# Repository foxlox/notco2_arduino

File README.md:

NotCO2 - A Co2 analyzer for rebreathers
=======================================
fortunato lodari - fox@thebrain.net

If you wish to write me by email, please use the tag [NOTCO2] (with brackets)
in your subject

Please read all DOCs carefully

Project borns in 2011 by a personal need, I'm a mathematical, then I can't leave an independent variable to change my life for a sport.
This independent variable is Carbon Dioxide, CO2. Then I decided to begin a new project to analyze my breathe underwater.

Till today, me and other many peoples are using it with satisfaction by over 6 years.
The sensor is working good for an average life of 5 years.

I received a lot of offers for my project, but I wish to share this with other peoples who want to hack.

Please do not be surprised reading the source code, I'm really (but really!) much more professional and tidy
than you consider me to look at it, it's really simple. It was born to hack, and then when it worked 100% I left it as it is.

It bores me to refine it and I'll not do it just now
that I want to share it ;-)
Now it's your time to refine it, but remember: it really works very well!!!

Documents:

a. layout of PCB and project to build it

b. required hardware components

c. source code HUD (never optimized, discreetly legible, absolutely improvable...)

d. source code Wrist Console (also fot it never optimized, discreetly legible, absolutely improvable...)

e. all DGWs to build your own enclosures with a 3d lathe machine

f. some pics

About CO2 Sensor: I cannot include device's interface specification without owner authorization, but you could try to ask
them: Dynament Ltd - www.dynament.com

  The sensor doesn't suffer with moisture, it's important to stay face down in the loop, and to be dry after diving.

Please, read ALL documents in each folder.

The Author is not responsible for damage to peoples that use this project.
It works perfectly but you must build it perfectly too.

Special thanks to:

Gabriele Paparo for hints, support and test

Martin Tolksdorf for enclosure and wrist project

Domenico Tripodi for support and experience during  diving tests

Saverio Rotella for HUD testing

Massimilaino Salvatori for hints

Sebastiano Pappalardo and Paolo Li Pera of Grade Equipments for HUD, wrist console and sensors enclosures

Gian Ameri for hints and support

Aldo Ferrucci for support

Franco Amadeo for diving support

My wonderful wife Mara for everything!

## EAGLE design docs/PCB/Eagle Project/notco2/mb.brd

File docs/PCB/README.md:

PCB information:
this is the project to build a PCB for NotCo2

Open with Eagles PCB. This release hasn't space for buzzer, could you insert it by yourself on arduino pin 3

connections:

SV2 pin 3, v+ in to battery v+

SV2 pin 1, v- -> to reed bulb -> to battery v-

SV2 pin 5, sensor tx

SV2 pin 6, sensor rx

Display

SV1 pin 1 TFT display VIN

SV1 pin 2 TFT display Ground

SV1 pin 3 RST

SV1 pin 4 RS

SV1 pin 5 SDA

SV1 pin 6 SDL

SV1 pin 7 CS

SV1 pin 8 TFT display VD33

HUD

SV2 pin 4, DIN

SV2 pin 3, led module v+

SV5 pin 2, led module v-

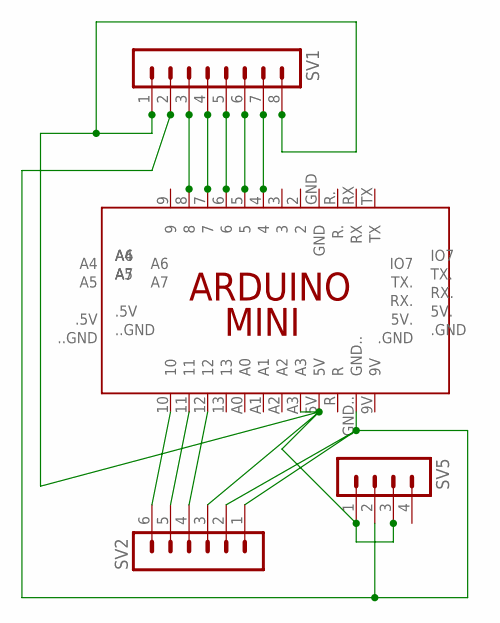
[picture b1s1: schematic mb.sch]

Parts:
PCB2: ARDUINO_MINI
SV1: MA08-1W
SV2: MA06-1
SV5: MA04-1

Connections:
unnamed: PCB2.8, SV1.3
unnamed: PCB2.7, SV1.4
unnamed: PCB2.6, SV1.5
unnamed: PCB2.5, SV1.6
unnamed: PCB2.4, SV1.7
unnamed: PCB2.5V, PCB2.A3, SV1.1, SV1.8, SV2.3, SV5.1, SV5.3
unnamed: PCB2.12, SV2.4
unnamed: PCB2.GND.., SV1.2, SV2.1, SV2.2, SV5.2
unnamed: PCB2.11, SV2.5
unnamed: PCB2.10, SV2.6

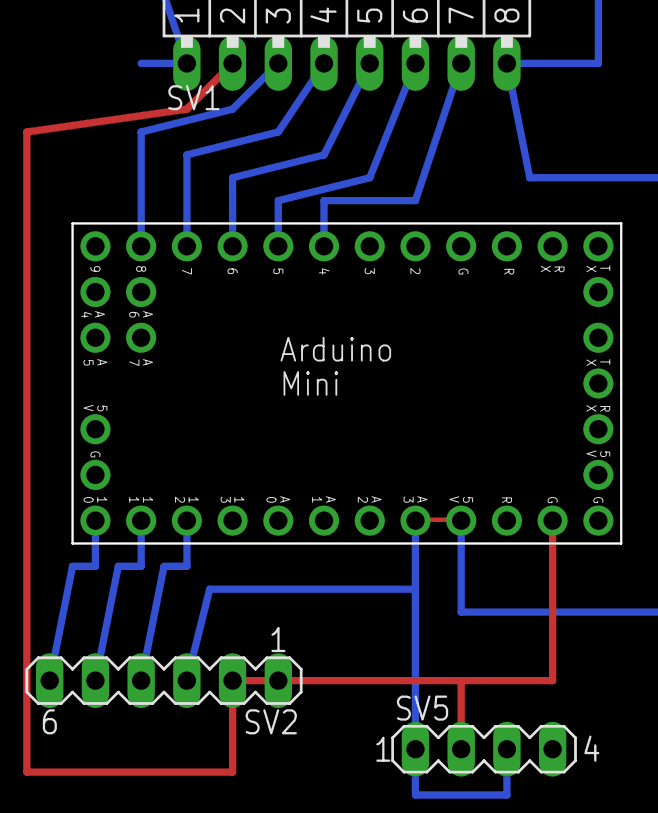
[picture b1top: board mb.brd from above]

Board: 2 copper layers, 4 parts (0 on the bottom side), 10 nets.

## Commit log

2019-02-04 final
2019-02-04 finale
